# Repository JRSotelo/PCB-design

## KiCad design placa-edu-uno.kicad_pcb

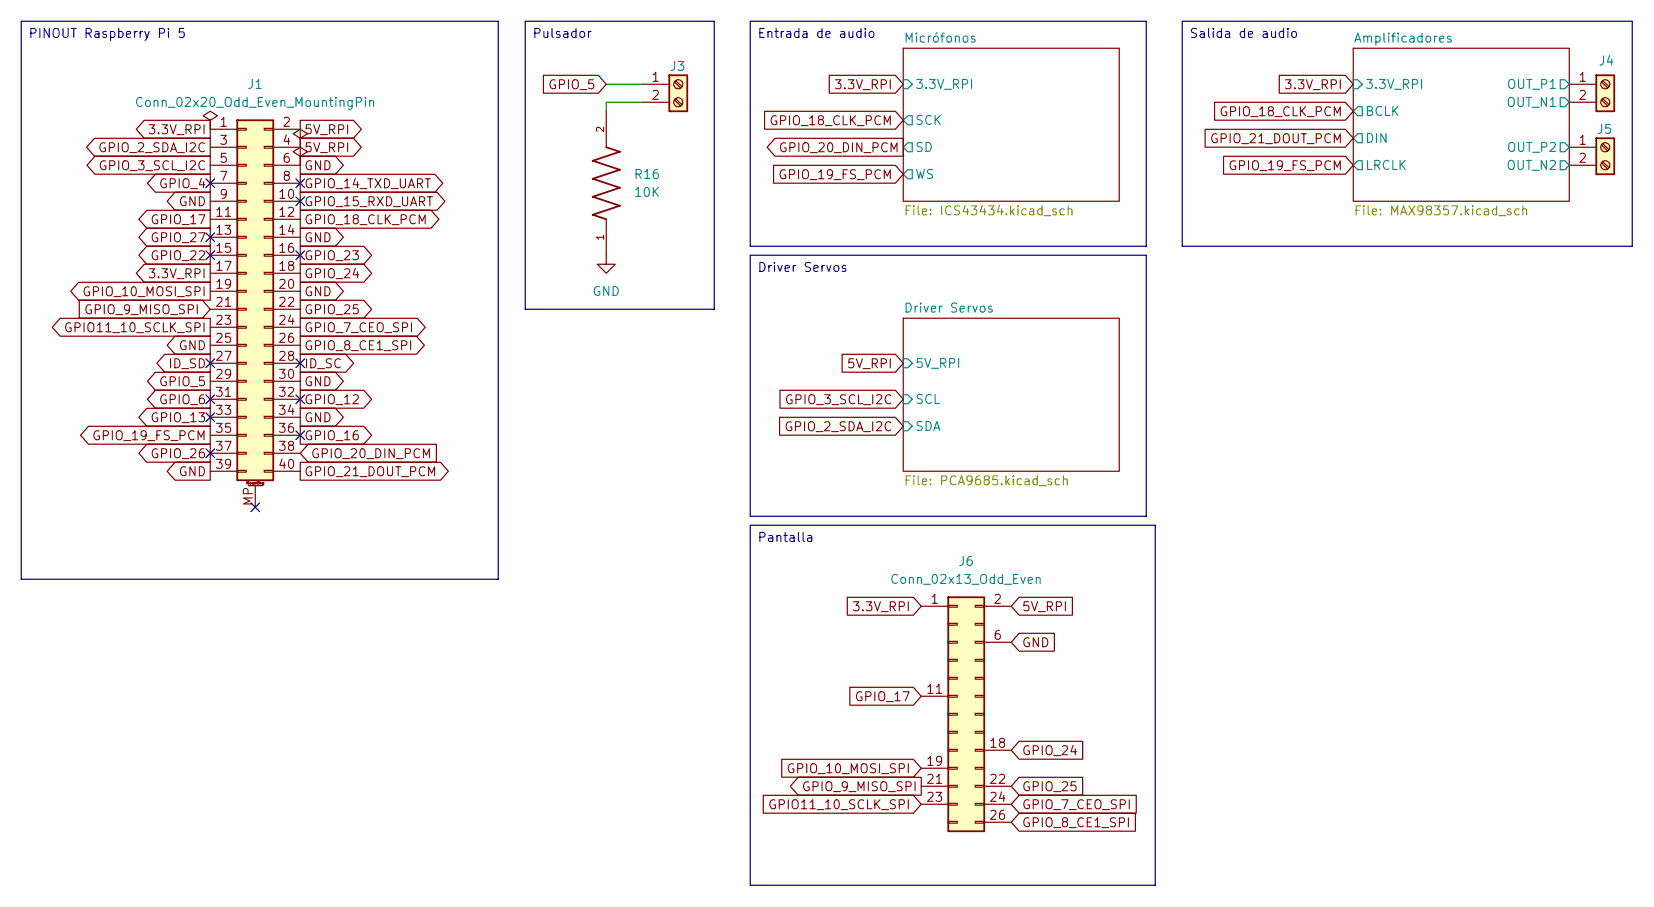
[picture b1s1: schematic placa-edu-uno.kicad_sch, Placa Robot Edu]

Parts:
J1: Conn_02x20_Odd_Even_MountingPin; Untitled
J3: Screw_Terminal_01x02; PinHeader_1x02_P2.54mm_Vertical
J4, J5: Screw_Terminal_01x02; PinHeader_1x02_P2.54mm_Vertical_Edited
J6: Conn_02x13_Odd_Even; SAMTEC_MTSW-113-09-L-D-500
R16: 10K; RESC1608X55N

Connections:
3.3V_RPI: J1.1, J1.17, J6.1; also elsewhere on the board
5V_RPI: J1.2, J1.4, J6.2; also elsewhere on the board
/Amplificadores/OUT_N1: J4.2; also elsewhere on the board
/Amplificadores/OUT_N2: J5.2; also elsewhere on the board
/Amplificadores/OUT_P1: J4.1; also elsewhere on the board
/Amplificadores/OUT_P2: J5.1; also elsewhere on the board
GND: J1.6, J1.9, J1.14, J1.20, J1.25, J1.30, J1.34, J1.39, J6.6, R16.1; also elsewhere on the board
GPIO11_10_SCLK_SPI: J1.23, J6.23
GPIO_2_SDA_I2C: J1.3; also elsewhere on the board
GPIO_3_SCL_I2C: J1.5; also elsewhere on the board
GPIO_4: J1.7
GPIO_5: J1.29, J3.1
GPIO_6: J1.31
GPIO_7_CEO_SPI: J1.24, J6.24
GPIO_8_CE1_SPI: J1.26, J6.26
GPIO_9_MISO_SPI: J1.21, J6.21
GPIO_10_MOSI_SPI: J1.19, J6.19
GPIO_12: J1.32
GPIO_13: J1.33
GPIO_14_TXD_UART: J1.8
GPIO_15_RXD_UART: J1.10
GPIO_16: J1.36
GPIO_17: J1.11, J6.11
GPIO_18_CLK_PCM: J1.12; also elsewhere on the board
GPIO_19_FS_PCM: J1.35; also elsewhere on the board
GPIO_20_DIN_PCM: J1.38; also elsewhere on the board
GPIO_21_DOUT_PCM: J1.40; also elsewhere on the board
GPIO_22: J1.15
GPIO_23: J1.16
GPIO_24: J1.18, J6.18
GPIO_25: J1.22, J6.22
GPIO_26: J1.37
GPIO_27: J1.13
ID_SC: J1.28
ID_SD: J1.27
unnamed: J3.2, R16.2

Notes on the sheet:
Pantalla
Pulsador
Driver Servos
PINOUT Raspberry Pi 5
Salida de audio
Entrada de audio

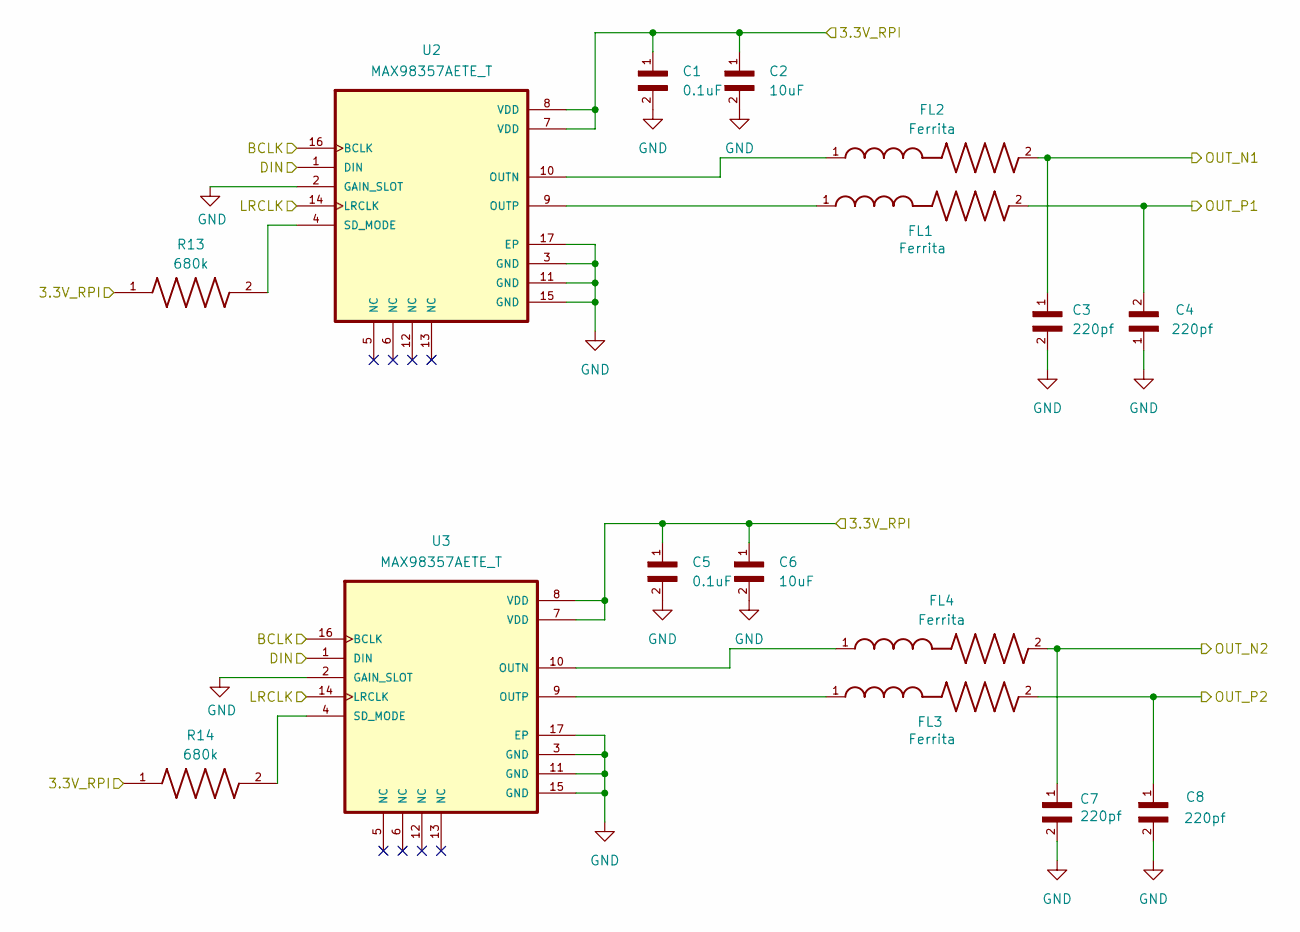
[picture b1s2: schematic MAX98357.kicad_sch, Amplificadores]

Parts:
C1, C5: 0.1uF; CAPC1005X55N
C2, C6: 10uF; CAPC2012X140N
C3, C4, C7, C8: 220pf; CAPC1608X90N
FL1, FL2, FL3, FL4: Ferrita; BEADC1608X95N
R13, R14: 680k; RESC1005X40N; PARTREV V3
U2, U3: MAX98357AETE_T; QFN50P300X300X80-17N

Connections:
3.3V_RPI: C1.1, C2.1, C5.1, C6.1, R13.1, R14.1, U2.7 (VDD), U2.8 (VDD), U3.7 (VDD), U3.8 (VDD); also elsewhere on the board
/Amplificadores/OUT_N1: C3.1, FL2.2; also elsewhere on the board
/Amplificadores/OUT_N2: C7.1, FL4.2; also elsewhere on the board
/Amplificadores/OUT_P1: C4.2, FL1.2; also elsewhere on the board
/Amplificadores/OUT_P2: C8.1, FL3.2; also elsewhere on the board
GND: C1.2, C2.2, C3.2, C4.1, C5.2, C6.2, C7.2, C8.2, U2.2 (GAIN_SLOT), U2.3 (GND), U2.11 (GND), U2.15 (GND), U2.17 (EP), U3.2 (GAIN_SLOT), U3.3 (GND), U3.11 (GND), U3.15 (GND), U3.17 (EP); also elsewhere on the board
GPIO_18_CLK_PCM: U2.16 (BCLK), U3.16 (BCLK); also elsewhere on the board
GPIO_19_FS_PCM: U2.14 (LRCLK), U3.14 (LRCLK); also elsewhere on the board
GPIO_21_DOUT_PCM: U2.1 (DIN), U3.1 (DIN); also elsewhere on the board
unnamed: FL2.1, U2.10 (OUTN)
unnamed: FL1.1, U2.9 (OUTP)
unnamed: R13.2, U2.4 (SD_MODE)
unnamed: FL4.1, U3.10 (OUTN)
unnamed: FL3.1, U3.9 (OUTP)
unnamed: R14.2, U3.4 (SD_MODE)

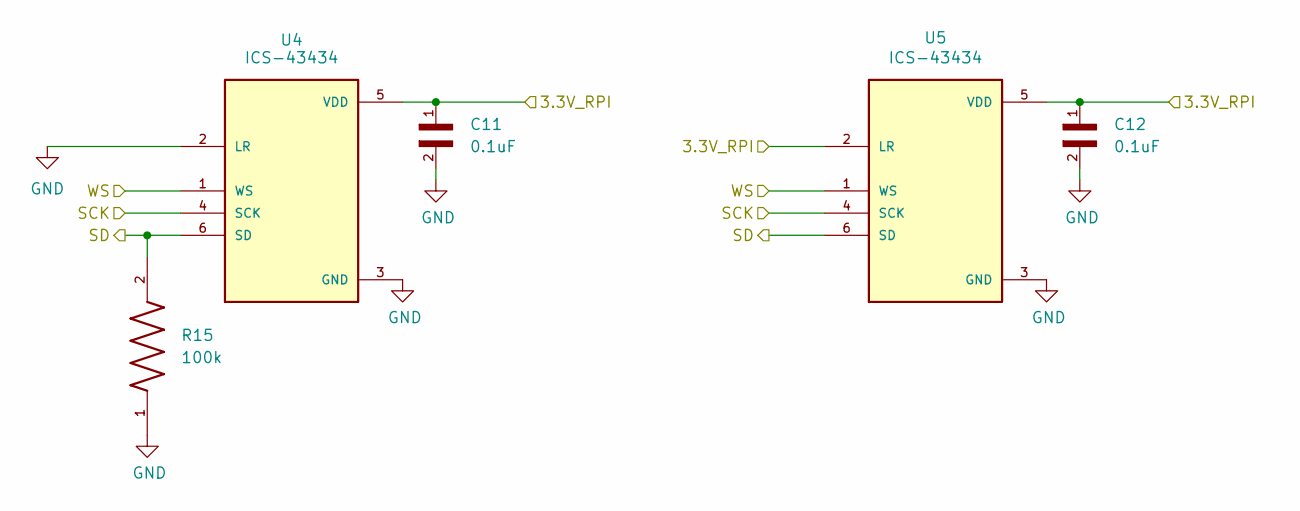
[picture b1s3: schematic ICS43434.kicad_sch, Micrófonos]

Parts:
C11, C12: 0.1uF; CAPC1005X55N
R15: 100k; RESC1608X55N; PARTREV V3
U4, U5: ICS-43434; MIC_ICS-43434

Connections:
3.3V_RPI: C11.1, C12.1, U4.5 (VDD), U5.2 (LR), U5.5 (VDD); also elsewhere on the board
GND: C11.2, C12.2, R15.1, U4.2 (LR), U4.3 (GND), U5.3 (GND); also elsewhere on the board
GPIO_18_CLK_PCM: U4.4 (SCK), U5.4 (SCK); also elsewhere on the board
GPIO_19_FS_PCM: U4.1 (WS), U5.1 (WS); also elsewhere on the board
GPIO_20_DIN_PCM: R15.2, U4.6 (SD), U5.6 (SD); also elsewhere on the board

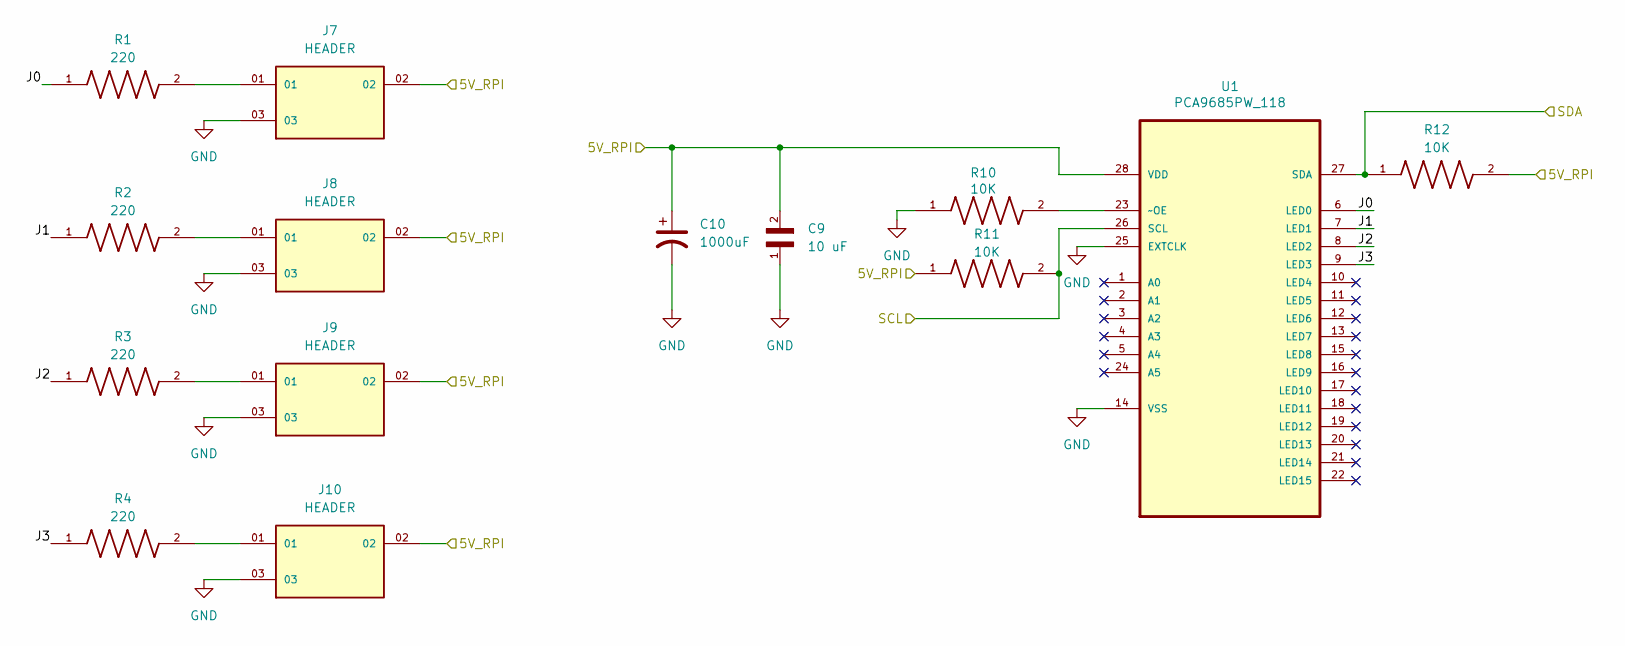
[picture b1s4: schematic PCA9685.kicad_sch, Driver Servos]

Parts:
C9: 10 uF; CAPC3216X180N
C10: 1000uF; CAPPRD500W60D1000H2500
J7, J8, J9, J10: HEADER; SAMTEC_TSW-101-07-T-T; PARTREV R
R1, R2, R3, R4: 220; RESC1005X40N
R10, R11, R12: 10K; RESC1608X55N
U1: PCA9685PW_118; SOP65P640X110-28N; MPN PCA9685PW,118

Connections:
5V_RPI: C9.2, C10.1, J7.02, J8.02, J9.02, J10.02, R11.1, R12.2, U1.28 (VDD); also elsewhere on the board
/Driver Servos/J0: R1.1, U1.6 (LED0)
/Driver Servos/J1: R2.1, U1.7 (LED1)
/Driver Servos/J2: R3.1, U1.8 (LED2)
/Driver Servos/J3: R4.1, U1.9 (LED3)
GND: C9.1, C10.2, J7.03, J8.03, J9.03, J10.03, R10.1, U1.14 (VSS), U1.25 (EXTCLK); also elsewhere on the board
GPIO_2_SDA_I2C: R12.1, U1.27 (SDA); also elsewhere on the board
GPIO_3_SCL_I2C: R11.2, U1.26 (SCL); also elsewhere on the board
unnamed: J7.01, R1.2
unnamed: J8.01, R2.2
unnamed: J9.01, R3.2
unnamed: J10.01, R4.2
unnamed: R10.2, U1.23 (~OE)

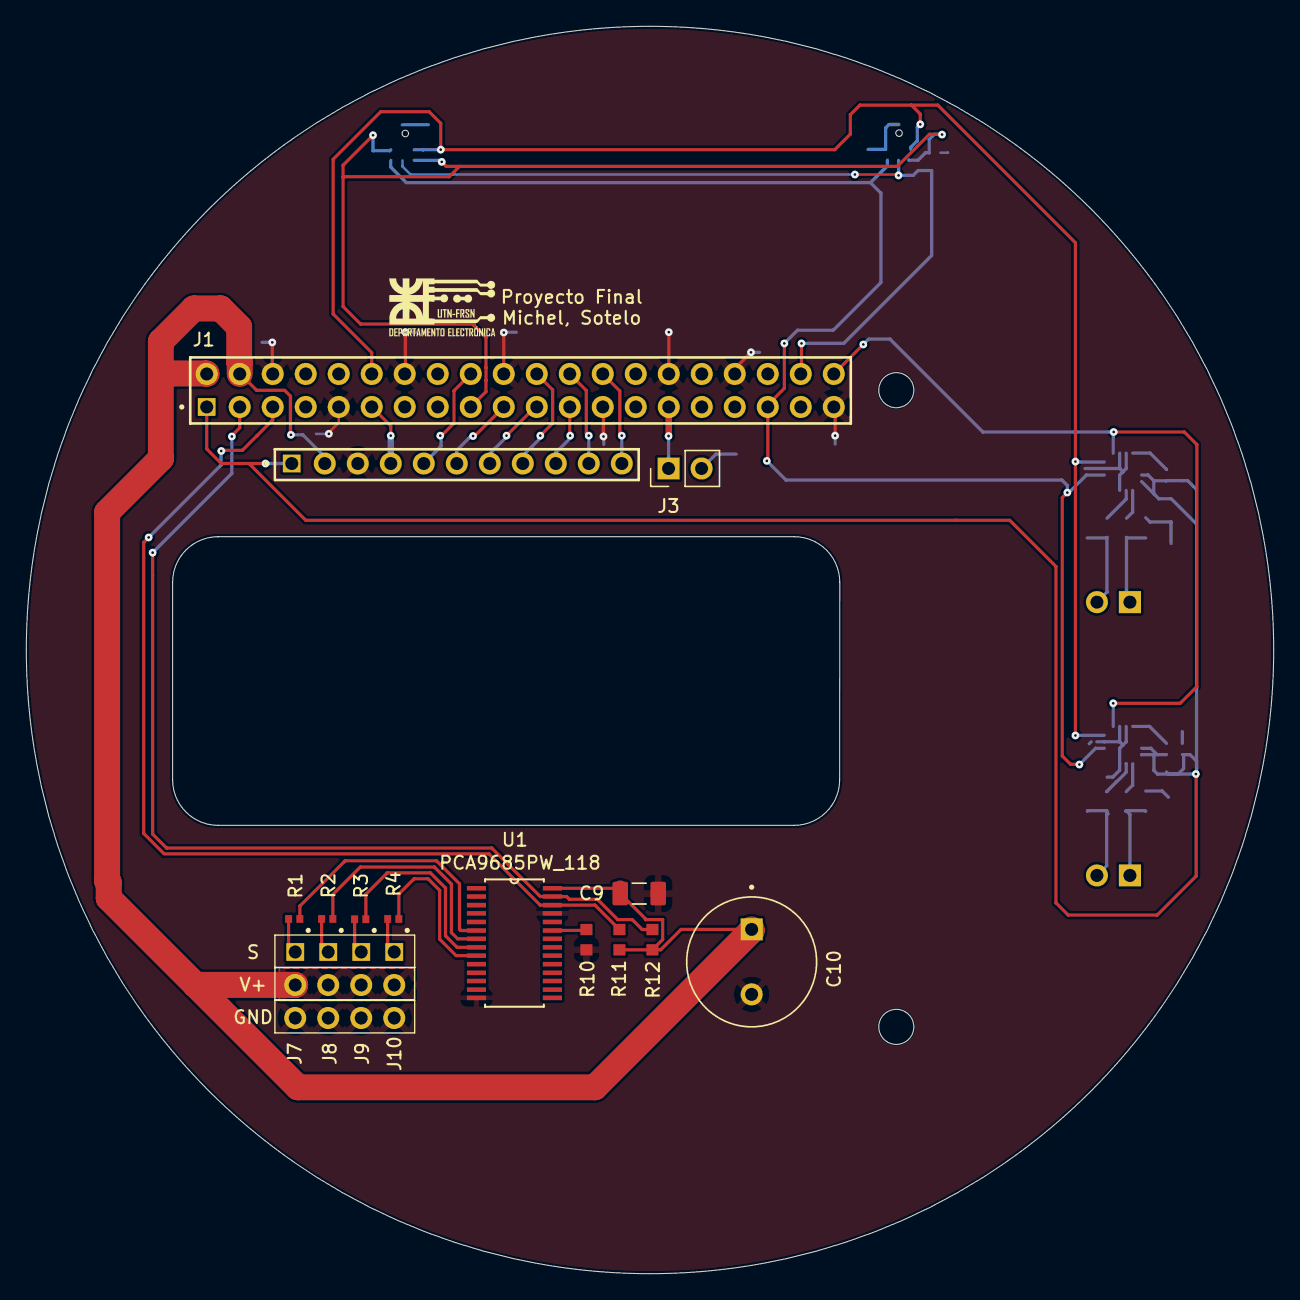
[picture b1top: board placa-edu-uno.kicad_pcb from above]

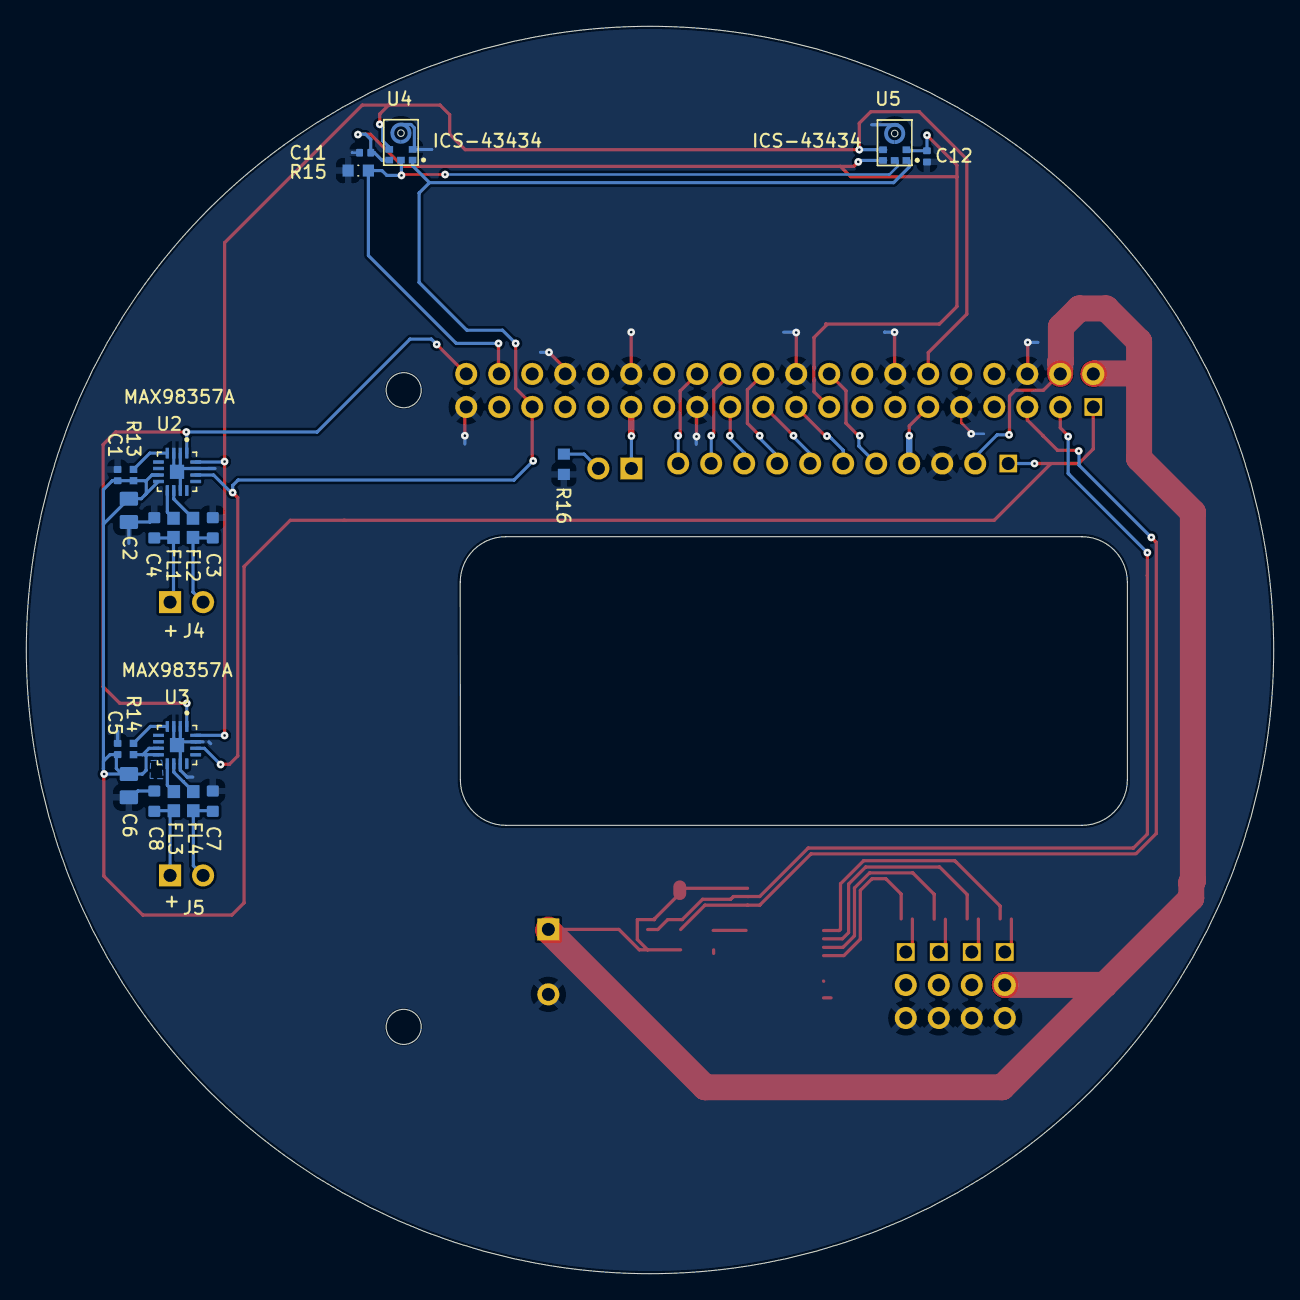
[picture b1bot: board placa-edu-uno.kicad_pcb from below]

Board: 2 copper layers, 96.0 x 96.0 mm, 43 parts (24 on the bottom side), 38 nets.

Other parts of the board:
MountingHole: MountingHole_2.7mm_M2.5
MountingHole#2: MountingHole_2.7mm_M2.5

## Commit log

2025-10-27 Se removio J4 y J5 de la serigrafia, se encontraba por error en ambas caras de la placa.
2025-10-27 Se agregó símbolo de polaridad a J2 en la serigrafía
2025-10-27 Se añadió serigrafía con nombres, logos y pines de los servos
2025-10-27 Se corrigio la posicion de la serigrafia en J4 y J5, y el nombre de la U1 PCA9685
2025-10-28 Mejora de ruteo
2025-10-29 Se movio la posicion de c y r en el amplificador de abajo para que no quede sobre el borde del mounting hole.
2025-10-30 Se arranca un nuevo diseno. Se saco el regulador y 4 servos. Hay que reajustar el diseno del PCB.
2025-10-31 Se borro todo y se arranco de nuevo. Placa circular.
2025-11-02 modelos 3D añadidos
2025-11-05 Se centraron los microfonos a 19 mm del centro de la placa
2025-11-06 Arreglo modelo 3d stackable header
